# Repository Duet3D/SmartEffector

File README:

The Duet3d Smart Effector design files repository.

See https://www.duet3d.com/DeltaSmartEffector for more information and to purchase a smart effector.

Duet3d Delta Smart Effector
Design by Tony Lock and David Crocker
LICENSE: see the LICENSE file in the repository
Documentation: https://docs.duet3d.com/Duet3D_hardware/Accessories/Smart_Effector
Discussion: https://www.duet3d.com/forum/

Developed in KiCAD: http://www.kicad-pcb.org/display/KICAD/KiCad+EDA+Software+Suite

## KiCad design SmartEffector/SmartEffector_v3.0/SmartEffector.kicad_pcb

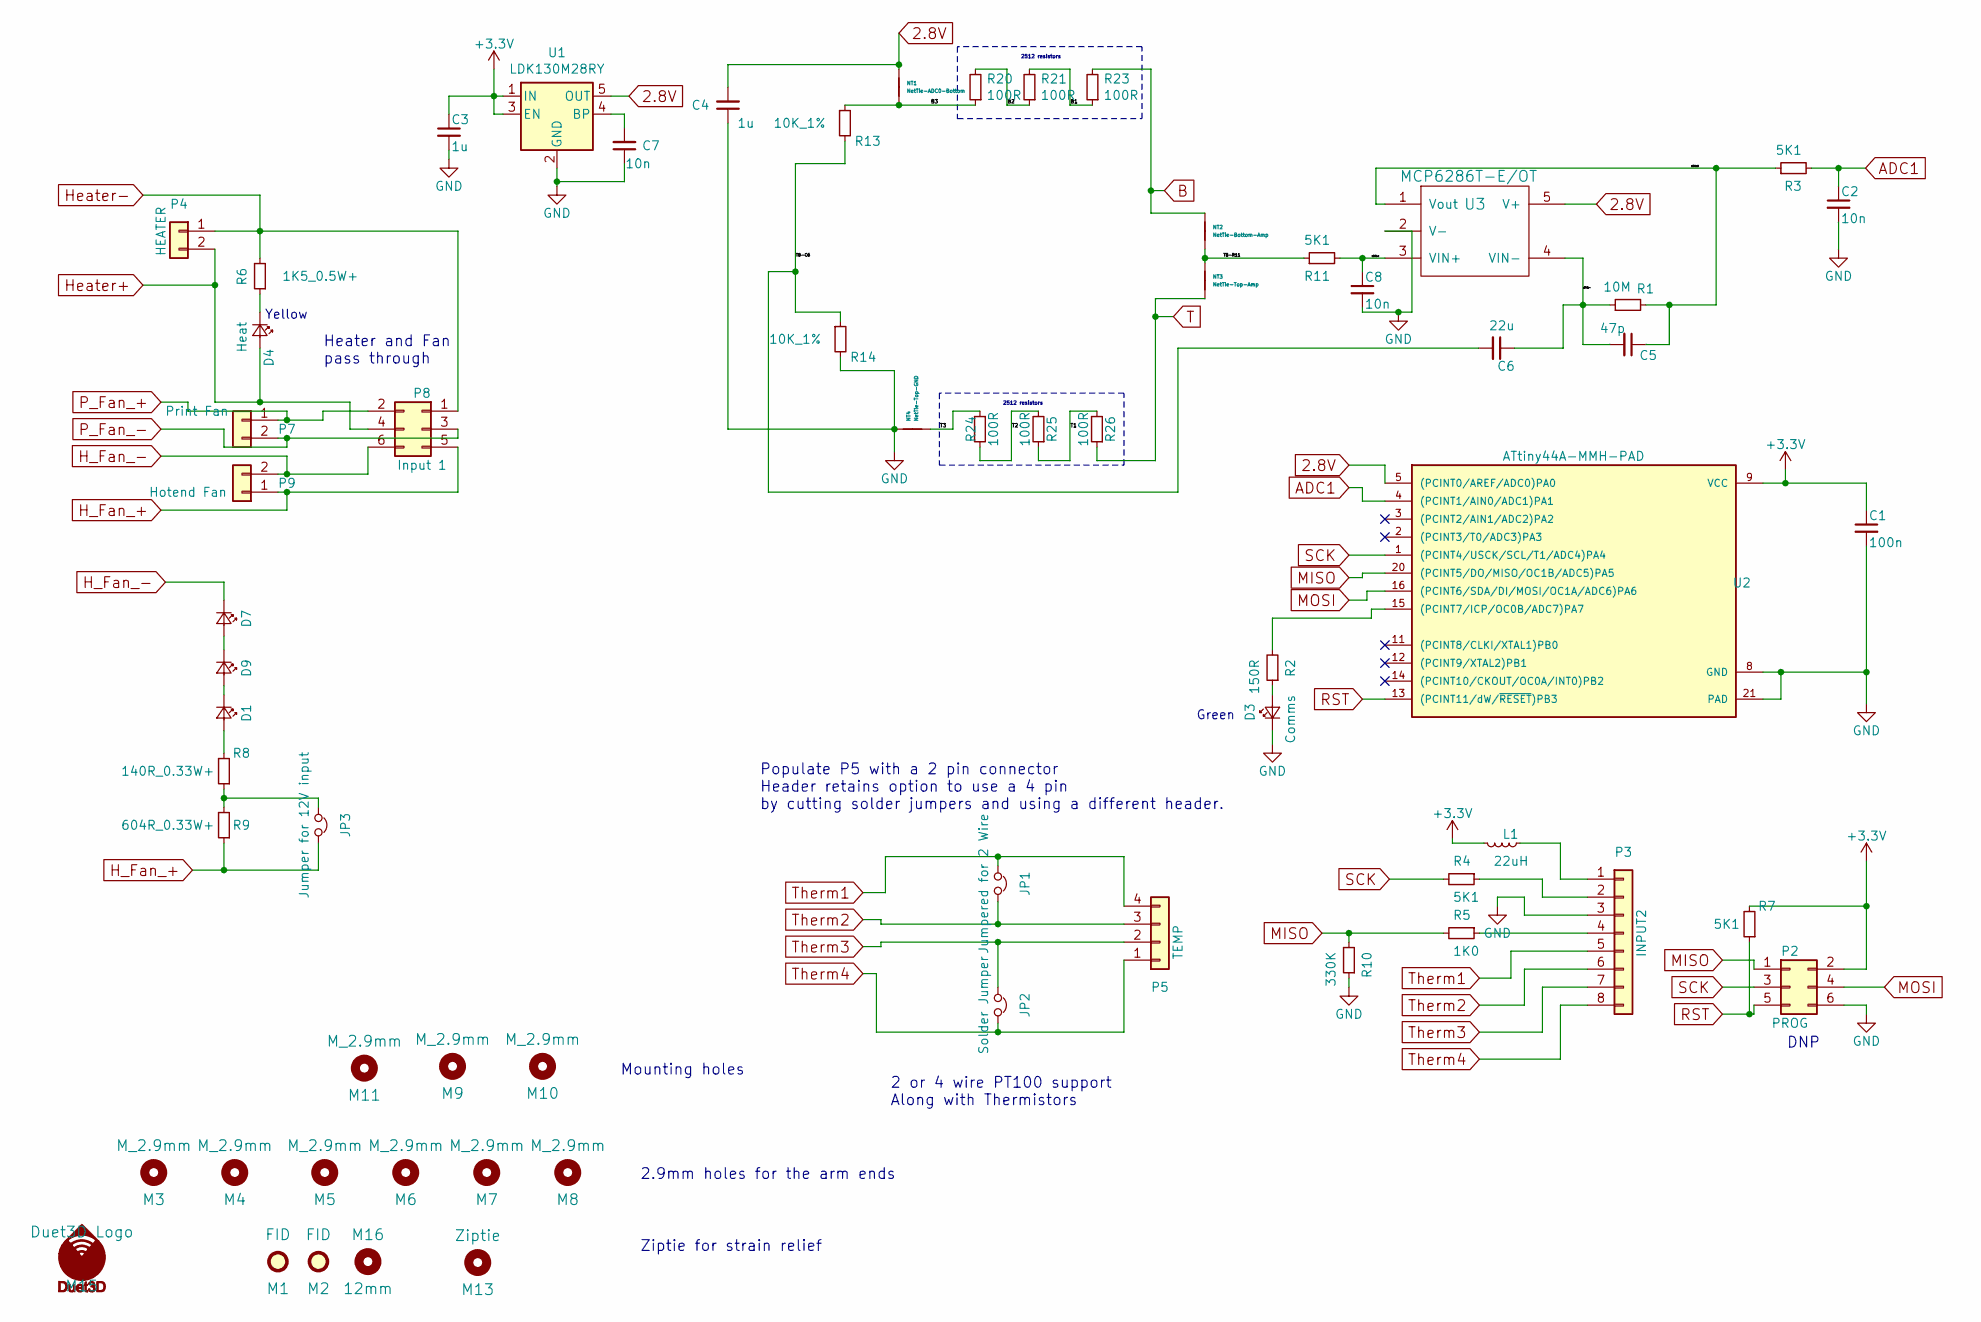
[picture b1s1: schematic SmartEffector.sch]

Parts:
C1: 100n; C_0402_1005Metric_Wbry; Part Number CL05A104KA5NNNC
C2, C7, C8: 10n; C_0402_1005Metric_Wbry; Part Number CL05B103KB5NNNC
C3, C4: 1u; C_0603_1608Metric_Wbry; Part Number CL10B105MO8NNWC
C5: 47p; C_0603_1608Metric_Wbry; Part Number 06035C470JAT2A
C6: 22u; C_0805_2012Metric; Part Number GRM21BR61A226ME51L or similar
D1, D7, D9: illum; LED_Wurth-158302260; Part Number 158302260
D3: Comms; LED_1206_bottom_entry_156120VS75000; Part Number 156120VS75000
D4: Heat; LED_1206_bottom_entry_156120VS75000; Part Number 156120YS75000
JP1: Jumpered for 2 Wire; SJ_Bridged; Part Number Virtual component DNP
JP2: Solder Jumper; SJ_Bridged; Part Number Virtual component DNP
JP3: Jumper for 12V input; JUMPER
L1: 22uH; L_0805_2012Metric; Part Number MLZ2012M220WT000
M1, M2: FID; Fiducial_1mm_Dia_2.54mm_Outer_CopperTop; Part Number Virtual component DNP
M3, M4, M5, M6, M7, M8, M9, M10, M11: M_2.9mm; MountingHole_2.9mm; Part Number Virtual component DNP
M13: Ziptie; Ziptie_small; Part Number Virtual component DNP
M15: Duet3D Logo; LOGO_Duet3d_CU_Mask; Part Number Virtual component DNP
M16: 12mm; 12mmHole; Part Number Virtual component DNP
NT1: NetTie-ADC0-Bottom; NetTie-2_SMD_Pad0.25mm; Part Number Virtual component DNP
NT2: NetTie-Bottom-Amp; NetTie-2_SMD_Pad0.5mm; Part Number Virtual component DNP
NT3: NetTie-Top-Amp; NetTie-2_SMD_Pad0.5mm; Part Number Virtual component DNP
NT4: NetTie-Top-GND; NetTie-2_SMD_Pad0.5mm; Part Number Virtual component DNP
P2: PROG; Test_Point_2x3; Part Number Virtual component DNP
P3: INPUT2; Molex_KK-254_AE-6410-08A_1x08_P2.54mm_Vertical
P4: HEATER; 3.5MM_2X1
P5: TEMP; Microfit_01x02or04_43650-0227
P7: Print Fan; Wurth_61900211121-1x02_P2.54mm_Vertical-(Molex_KK-254_AE-64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
P8: Input 1; Microfit_02x03
P9: Hotend Fan; Microfit_01x02_43650-0227
R1: 10M; R_0603_1608Metric_Wbry; Part Number RMCF0603JG10M0
R2: 150R; R_0402_1005Metric_Wbry; Part Number RC0402FR-07150RL
R3, R4, R7, R11: 5K1; R_0402_1005Metric_Wbry; Part Number RMCF0402FT5K10
R5: 1K0; R_0402_1005Metric_Wbry; Part Number CR0402-FX-1001GLF
R6: 1K5_0.5W+; R_1206; Part Number CRGH1206F1K5
R8: 140R_0.33W+; R_0805_extended_pads; Part Number ERJP06F1400V
R9: 604R_0.33W+; R_1206_3216Metric; Part Number RNCP1206FTD604R
R10: 330K; R_0402_1005Metric_Wbry; Part Number RMCF0402FT330K
R13, R14: 10K_1%; R_0402_1005Metric_Wbry; Part Number RK73H1ETTP1002F
R20, R21, R23, R24, R25, R26: 100R; R_2512_6332Metric; Part Number CRCW2512100RFKEG
U1: LDK130M28RY; SOT-23-5L; Part Number LDK130M28RY with LDK130M29R as an alter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
U2: ATtiny44A-MMH-PAD; QFN-20-1EP_4x4mm_Pitch0.5mm; Part Number ATtiny44A-MUR
U3: MCP6286T-E/OT; SOT-23-5L; Part Number OPA377AIDBVR preferred, possible to rev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

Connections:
2.8V: C4.2, NT1.1, U1.5 (OUT), U2.5 ((PCINT0/AREF/ADC0)PA0), U3.5 (V+)
+3V3: C1.1, C3.1, L1.2, P2.2, R7.2, U1.1 (IN), U1.3 (EN), U2.9 (VCC)
/B1: R21.2, R23.1
/B2: R20.2, R21.1
/B3: NT1.2, R13.1, R20.1
/T1: R25.1, R26.2
/T2: R24.2, R25.2
/T3: NT4.2, R24.1
/TB-C6: C6.2, R13.2, R14.1
/TB-R11: NT2.2, NT3.1, R11.1
/u3Vout: C5.1, R1.2, R3.1, U3.1 (Vout)
/u3vin+: C8.1, R11.2, U3.3 (VIN+)
/u3vin-: C5.2, C6.1, R1.1, U3.4 (VIN-)
ADC1: C2.1, R3.2, U2.4 ((PCINT1/AIN0/ADC1)PA1)
B: NT2.1, R23.2
GND: C1.2, C2.2, C3.2, C4.1, C7.1, C8.2, D3.1 (K), NT4.1, P2.6, P3.3, R10.1, R14.2, U1.2 (GND), U2.8 (GND), U2.21 (PAD), U3.2 (V-)
H_Fan_+: JP3.2, P8.5, P9.1, R9.1
H_Fan_-: D7.1 (K), P8.6, P9.2
Heater+: D4.2 (A), P4.2, P8.4
Heater-: P4.1, P8.1, R6.2
MISO: P2.1, R5.2, R10.2, U2.20 ((PCINT5/DO/MISO/OC1B/ADC5)PA5)
MOSI: P2.4, U2.16 ((PCINT6/SDA/DI/MOSI/OC1A/ADC6)PA6)
unnamed: C7.2, U1.4 (BP)
unnamed: D1.1 (K), D9.2 (A)
unnamed: D1.2 (A), R8.2
unnamed: D3.2 (A), R2.1
unnamed: D4.1 (K), R6.1
unnamed: D7.2 (A), D9.1 (K)
unnamed: JP3.1, R8.1, R9.2
unnamed: L1.1, P3.1
unnamed: P3.2, R4.1
unnamed: P3.4, R5.1
unnamed: R2.2, U2.15 ((PCINT7/ICP/OC0B/ADC7)PA7)
P_Fan_+: P7.1, P8.2
P_Fan_-: P7.2, P8.3
RST: P2.5, R7.1, U2.13 ((PCINT11/dW/~RESET~)PB3)
SCK: P2.3, R4.2, U2.1 ((PCINT4/USCK/SCL/T1/ADC4)PA4)
T: NT3.2, R26.1
Therm1: JP1.1, P3.5, P5.4
Therm2: JP1.2, P3.6, P5.3
Therm3: JP2.1, P3.7, P5.2
Therm4: JP2.2, P3.8, P5.1

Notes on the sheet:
DNP
Heater and Fan pass through
2.9mm holes for the arm ends
Ziptie for strain relief
2 or 4 wire PT100 support Along with Thermistors
Populate P5 with a 2 pin connector Header retains option to use a 4 pin by cutting solder jumpers and using a different header.
Mounting holes
2512 resistors
Yellow
Green

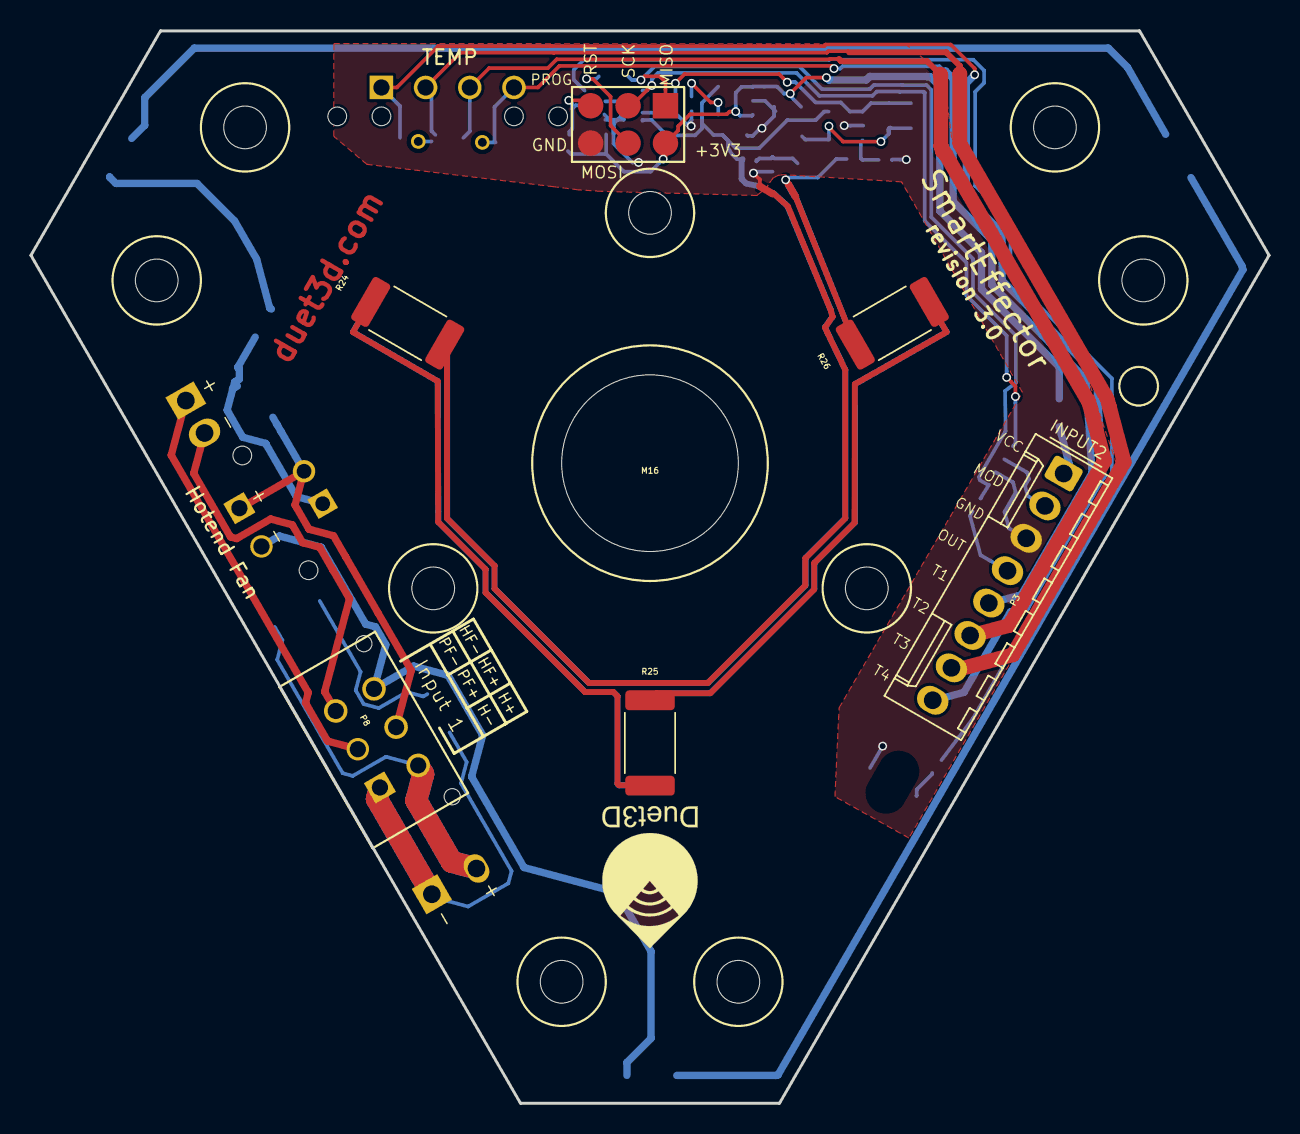
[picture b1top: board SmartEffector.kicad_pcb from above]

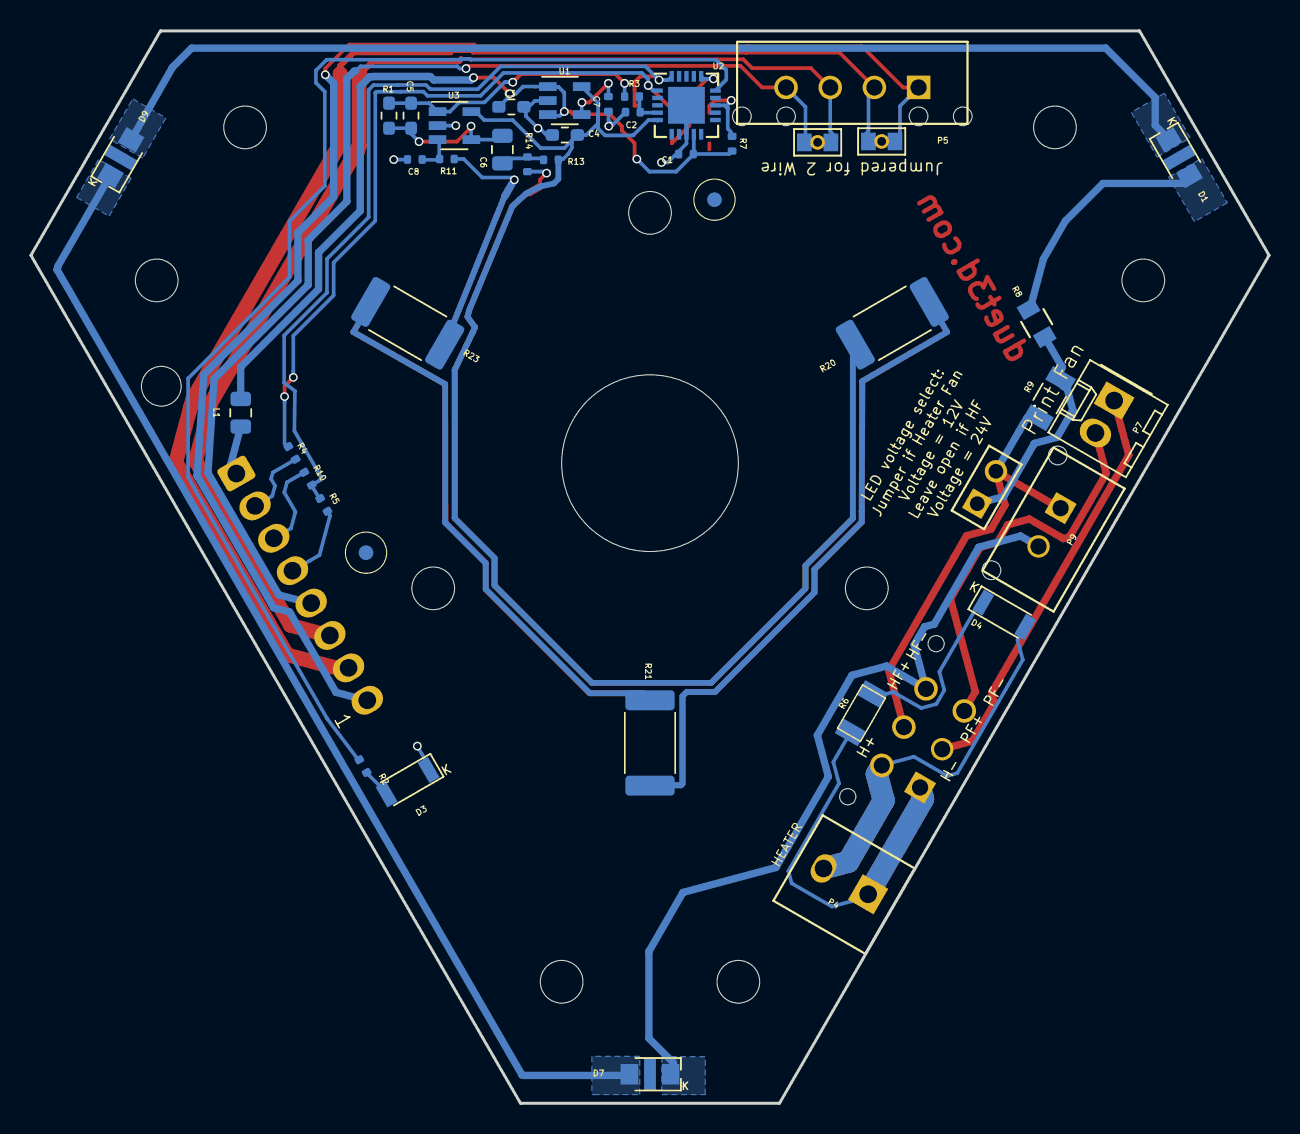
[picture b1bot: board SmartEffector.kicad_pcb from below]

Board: 2 copper layers, 84.1 x 72.8 mm, 64 parts (44 on the bottom side), 42 nets.

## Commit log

2017-09-05 :neckbeard: Added .gitattributes & .gitignore files
2017-09-05 Added License and Readme
2017-09-05 Smart Effector version 1.3
    Initial production model
2017-09-05 Carriage Adaptor for Delta Smart Effector
2018-03-06 Updated documentation link
2019-06-02 Update LICENSE
    Changed to Reflect Duet3D Ltd
2019-06-02 SmartEffector 2.0 KiCAD source added
2021-03-19 Updated some schematic issues
2021-08-02 Smart Effector v3.0 source files and STEP
2025-01-20 v4.0 Schematic

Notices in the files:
SmartEffector/SmartEffector_v2.0/SmartEffector.sch:
CERN OHL 1.2
